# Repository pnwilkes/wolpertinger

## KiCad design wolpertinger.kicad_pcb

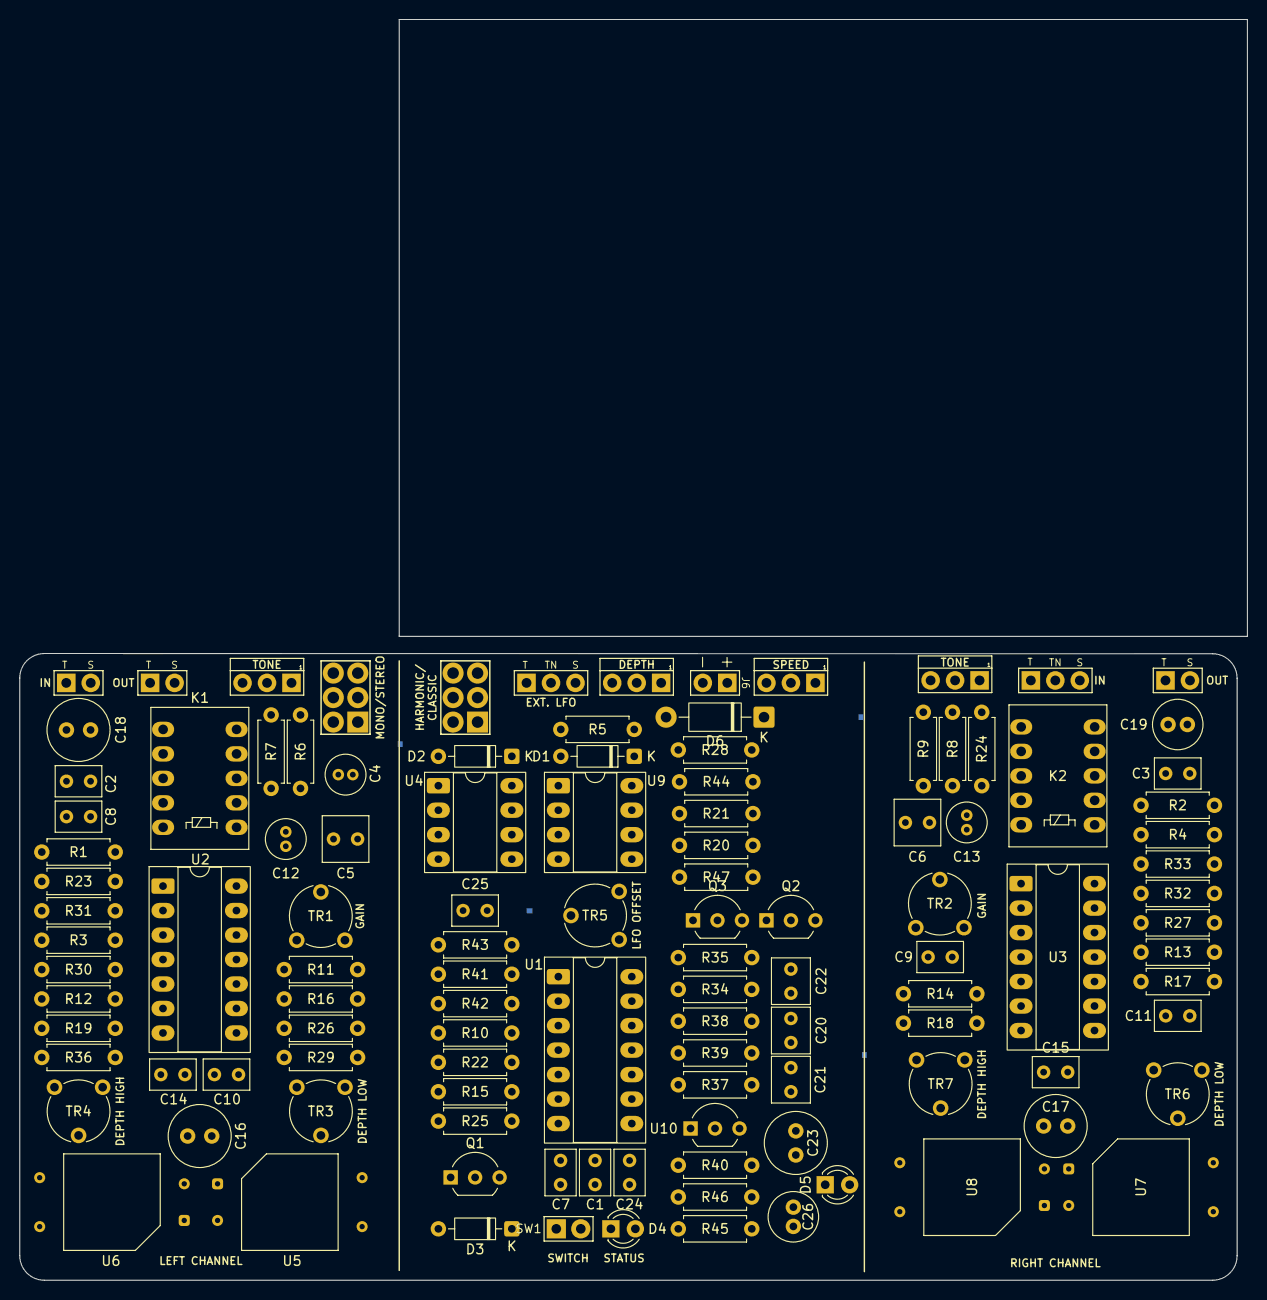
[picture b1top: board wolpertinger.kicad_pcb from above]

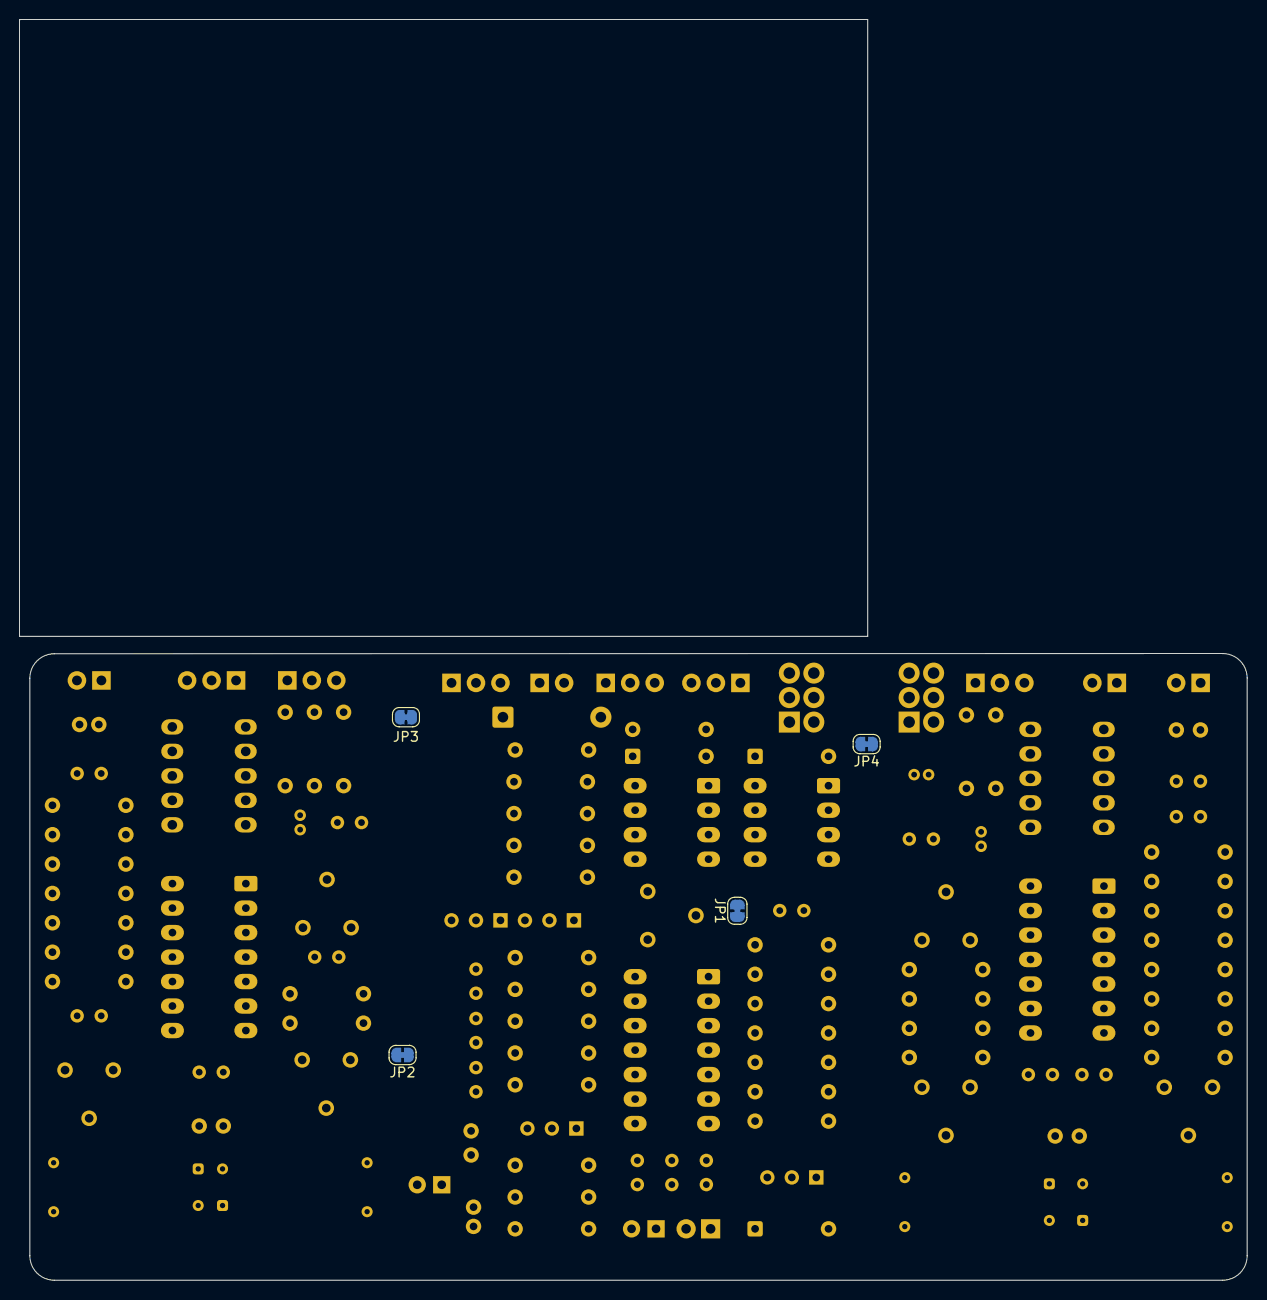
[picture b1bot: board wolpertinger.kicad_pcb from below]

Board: 2 copper layers, 127.3 x 130.8 mm, 118 parts (4 on the bottom side), 82 nets, no tracks yet.

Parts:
C1, C2, C3, C7, C14, C15, C24, C25: 100nF; C_Rect_L4.6mm_W3.0mm_P2.50mm_MKS02_FKP02
C4, C12, C13: 10uF; C_Radial_D4.0mm_H7.0mm_P1.50mm
C5, C6: 470nF; C_Rect_L4.6mm_W4.6mm_P2.50mm_MKS02_FKP02
C8, C9: 6.8nF; C_Rect_L4.6mm_W3.0mm_P2.50mm_MKS02_FKP02
C10, C11: 4.7nF; C_Rect_L4.6mm_W3.0mm_P2.50mm_MKS02_FKP02
C16, C17, C23: 100uF; C_Radial_D6.3mm_H11.0mm_P2.50mm
C18: 47uF; C_Radial_D6.3mm_H11.0mm_P2.50mm
C19, C26: 47uF; C_Radial_D5.0mm_H11.0mm_P2.00mm
C20, C21, C22: 330nF; C_Rect_L4.6mm_W3.8mm_P2.50mm_MKS02_FKP02
D1, D2: BAT42; D_DO-35_SOD27_P7.62mm_Horizontal
D3: 1N4148; D_DO-35_SOD27_P7.62mm_Horizontal
D4: STATUS LED; LED_D3.0mm
D5: TBD; LED_D3.0mm
D6: 1N4001; D_DO-41_SOD81_P10.16mm_Horizontal
J1: RIGHT IN; Switched Mono Jack
J2: LEFT IN; TWO_PADS
J3: EXT LFO; Switched Mono Jack
J4: LEFT OUT; TWO_PADS
J5: RIGHT OUT; TWO_PADS
J6: Jack-DC; BATTERY
JP1, JP2, JP3, JP4: SolderJumper-2_P1.3mm_Bridged_RoundedPad1.0x1.5mm
K1, K2: FRT5; Relay_DPDT_FRT5
Q1: BC549; TO-92_Inline_Wide
Q2, Q3: BC547; TO-92_Inline_Wide
R1, R2, R3, R4, R10, R23, R24: 1M; R_Axial_DIN0207_L6.3mm_D2.5mm_P7.62mm_Horizontal
R5, R15, R20, R21, R25, R37, R41, R42, R43: 10k; R_Axial_DIN0207_L6.3mm_D2.5mm_P7.62mm_Horizontal
R6, R7, R8, R9, R11, R12, R13, R14: 15K; R_Axial_DIN0207_L6.3mm_D2.5mm_P7.62mm_Horizontal
R16, R17, R18, R19: 51K; R_Axial_DIN0207_L6.3mm_D2.5mm_P7.62mm_Horizontal
R22, R28, R39: 4k7; R_Axial_DIN0207_L6.3mm_D2.5mm_P7.62mm_Horizontal
R26, R27, R40: 33r; R_Axial_DIN0207_L6.3mm_D2.5mm_P7.62mm_Horizontal
R29, R36, R44, R47: 100r; R_Axial_DIN0207_L6.3mm_D2.5mm_P7.62mm_Horizontal
R30, R31, R32, R33, R45, R46: 100k; R_Axial_DIN0207_L6.3mm_D2.5mm_P7.62mm_Horizontal
R34: 22k; R_Axial_DIN0207_L6.3mm_D2.5mm_P7.62mm_Horizontal
R35: 3M3; R_Axial_DIN0207_L6.3mm_D2.5mm_P7.62mm_Horizontal
R38: TBD; R_Axial_DIN0207_L6.3mm_D2.5mm_P7.62mm_Horizontal
RV1: 100k B; 16MM_PADS.1
RV2, RV3: 10k B; 16MM_PADS.1
RV4: 100k C; 16MM_PADS.1
SW1: ON/OFF; SPST
SW2: DPDT MONO/STEREO; DPDT
SW3: DPDT HARMONIC/TREMOLO; DPDT
TR1, TR2: VOLUME Trim 50k; Potentiometer_Piher_PT-6-V_Vertical
TR3: LO L Trim 5k; Potentiometer_Piher_PT-6-V_Vertical
TR4: HI L Trim 5k; Potentiometer_Piher_PT-6-V_Vertical
TR5: OFFSET Trim 25k; Potentiometer_Piher_PT-6-V_Vertical
TR6: LO R Trim 5k; Potentiometer_Piher_PT-6-V_Vertical
TR7: HI R Trim 5k; Potentiometer_Piher_PT-6-V_Vertical
U1: 4093; CERDIP-14_W7.62mm_SideBrazed_LongPads_Socket
U2, U3: TL074; CERDIP-14_W7.62mm_SideBrazed_LongPads_Socket
U4, U9: NE5532; DIP-8_W7.62mm_Socket_LongPads
U5, U6, U7, U8: VTL5C; PerkinElmer_VTL5C
U10: L78L05_TO92; TO-92_Inline_Wide

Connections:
9V: C1.1, D3.1 (K), D4.2 (A), D6.1 (K), J6.2, K1.1, K2.1, R26.1, R27.1, R40.1, U1.14 (Vdd)
BYPASS L: J2.T, K1.2, K1.7
BYPASS R: J1.T, K2.4, K2.9
GND: D6.2 (A), J6.1, JP1.2 (B), JP2.2 (B), JP3.2 (B), JP4.2 (B)
GND1: C14.1, C16.2, C18.2, J2.S, J4.S, JP4.1 (A), K1.9, R1.2, R23.2, R31.2, U2.11 (V-)
GND2: C15.1, C17.2, C19.2, J1.S, J5.S, JP3.1 (A), K2.2, R2.2, R24.2, R33.2, U3.11 (V-)
GND3: C23.2, C24.1, C26.2, D2.2 (A), D5.1 (K), J3.S, JP2.1 (A), Q2.3 (E), R28.2, R34.2, R39.2, R46.2, TR5.3, U4.4 (V-), U5.1 (-), U6.1 (-), U7.1 (-), U8.1 (-), U9.4 (V-)
GND4: C1.2, C7.2, JP1.1 (A), Q1.3 (E), U1.7 (Vss), U1.8, U1.9, U1.12, U1.13
LFO: C25.1, J3.TN, R43.1, U9.1
LFO out: R21.1, SW2.3 (C), SW2.4 (A), SW3.3 (C), U9.7
LFO out inv: R20.2, R47.1, SW2.1 (A), SW2.6 (C), SW3.1 (A), U4.6 (-), U4.7
MONO IN: C4.2, J1.TN
unnamed: C2.1, K1.8, R1.1
unnamed: C3.1, K2.3, R2.1
unnamed: C5.2, R6.2, R7.2
unnamed: C6.2, R8.2, R9.2
unnamed: C8.1, R7.1, RV2.3
unnamed: C8.2, R12.1
unnamed: C9.1, R9.1, RV3.3
unnamed: C9.2, R14.1
unnamed: C10.2, R16.2, U2.8, U5.3
unnamed: C11.2, R17.2, U3.8, U7.3
unnamed: C12.1, TR1.1, TR1.2, U2.14
unnamed: C12.2, K1.4, R23.1
unnamed: C13.1, TR2.1, TR2.2, U3.1
unnamed: C13.2, K2.7, R24.1
unnamed: C20.1, C22.2, R34.1
unnamed: C20.2, C21.2, RV4.1, RV4.2
unnamed: D1.2 (A), D2.1 (K), R5.2, RV1.1
unnamed: D3.2 (A), K1.10, K2.10, Q1.1 (C), R25.1
unnamed: D4.1 (K), R25.2
unnamed: D5.2 (A), U10.2 (GND)
unnamed: J3.T, R5.1
unnamed: J4.T, K1.3
unnamed: J5.T, K2.8
unnamed: Q1.2 (B), R22.2
unnamed: C22.1, Q2.2 (B), R35.2
unnamed: Q2.1 (C), Q3.2 (B), R35.1, R37.2
unnamed: C21.1, Q3.3 (E), R38.1
unnamed: R6.1, R11.1, RV2.1
unnamed: R8.1, R13.1, RV3.1
unnamed: R15.2, U1.3
unnamed: R18.1, U3.7, U8.3
unnamed: R19.1, U2.7, U6.3
unnamed: R28.1, RV4.3
unnamed: R29.2, TR3.1, TR3.2
unnamed: R36.2, TR4.1, TR4.2
unnamed: R38.2, R39.1, R42.2
unnamed: R41.2, TR5.2
unnamed: R44.2, TR6.1, TR6.2
unnamed: R47.2, TR7.1, TR7.2
unnamed: C7.1, R10.1, SW1.1 (A)
unnamed: R15.1, SW1.2 (B), U1.5, U1.6
unnamed: SW2.2 (B), SW3.6 (C)
unnamed: R36.1, SW2.5 (B), SW3.4 (A)
unnamed: R44.1, SW3.2 (B)
unnamed: R29.1, SW3.5 (B)
unnamed: C2.2, R3.2, U2.3 (+)
unnamed: C4.1, C5.1, U2.1, U2.2 (-)
unnamed: R12.2, R19.2, U2.6 (-)
unnamed: C10.1, R11.2, R16.1, U2.9 (-)
unnamed: TR1.3, U2.13 (-), U5.4, U6.4
unnamed: TR2.3, U3.2 (-), U7.4, U8.4
unnamed: R14.2, R18.2, U3.6 (-)
unnamed: C11.1, R13.2, R17.1, U3.9 (-)
unnamed: C3.2, R4.2, U3.12 (+)
unnamed: C6.1, U3.13 (-), U3.14
unnamed: RV1.2, U4.5 (+)
unnamed: C25.2, R41.1, R42.1, R43.2, U9.2 (-)
unnamed: R20.1, R21.2, U9.6 (-)
unnamed: C23.1, R40.2, U10.3 (VI)
ON/OFF: R10.2, R22.1, U1.1, U1.2, U1.4
V1: C14.2, C16.1, R26.2, R30.1, U2.4 (V+)
V2: C15.2, C17.1, R27.2, R32.1, U3.4 (V+)
V3: C24.2, D1.1 (K), Q3.1 (C), R37.1, R45.1, TR5.1, U4.8 (V+), U9.8 (V+), U10.1 (VO)
Vref1: C18.1, R3.1, R30.2, R31.1, RV2.2, U2.5 (+), U2.10 (+), U2.12 (+)
Vref2: C19.1, R4.1, R32.2, R33.1, RV3.2, U3.3 (+), U3.5 (+), U3.10 (+)
Vref3: C26.1, R45.2, R46.1, RV1.3, U9.3 (+), U9.5 (+)
hiL: TR4.3, U6.2 (+)
hiR: TR7.3, U8.2 (+)
loL: TR3.3, U5.2 (+)
loR: TR6.3, U7.2 (+)

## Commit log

2025-09-25 Init kicad
2025-09-25 add gitignore and schematic cleanup
2025-09-25 Add second channel and true bypass relay switching
2025-09-25 section cleanup
2025-09-25 Added PCB, Footprint cleanup
2025-09-25 Add footprints
2025-09-26 add power supply
2025-09-26 add different power supply grounds
2025-09-28 Add internal LFO
2025-09-28 cleanup power supply, add lfo voltage offset
2025-10-14 add custom part libary and add mode switch
2025-10-19 remove hi and low only mode in favor of simpler switches
2025-10-19 Add in mono to stereo out option
2025-10-19 Add Footprints pt1
2025-10-19 update pcb
2025-10-19 Add LED footprint
2025-10-19 Add DC Jk Footprint
2025-10-19 Add capacitors footprint
2025-10-19 Update jack footprints
2025-10-20 fix footprint pad errors
2025-10-21 Left channel layout
2025-10-21 Right channel
2025-10-31 populate pcb
2025-11-02 layout work
2025-11-02 verifiy film cap footprints and transistor footprints
2025-11-02 fix short
2025-11-02 add wide transistor footprint
2025-11-17 minor position adjustments
2025-11-23 parts aligning pt1
2025-11-25 add readme content
2025-11-25 adjust readme
2025-11-25 readme adjustments
2025-11-25 GND improvements
